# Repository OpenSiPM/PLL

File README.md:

## Overview

Resonant scanning is essential for high-speed and *in vivo* laser scanning microscopy. However, resonant scanners are susceptible to jitter due to a mismatch between the mirror's mechanical oscillation and the data acquisition system's pixel sampling clock. If the digitizer samples at a fixed rate, the pixels on one line land in slightly different positions than on the next and the raw data appears shifted from line to line.

Our solution is to generate the digitizer sample clock **from the resonant scanner's own sync signal** using a PLL. Every line is then sampled at the same scanner phase, so the pixel grid follows the scanner rather than drifting against it. The method runs in real time, is entirely electrical and requires no software changes, so it can be easily incorporated into most existing microscopy systems. 

This approach is described and validated in:

> Ching-Roa VD, Huang CZ, Giacomelli MG. **Suppression of Subpixel Jitter in Resonant Scanning Systems With Phase-locked Sampling.** *IEEE Transactions on Medical Imaging* 43(6):2159–2168, 2024. [doi:10.1109/TMI.2024.3358191](https://doi.org/10.1109/TMI.2024.3358191) · [PubMed 38265914](https://pubmed.ncbi.nlm.nih.gov/38265914/)

The repository is organized into separate folders: PLL_AD9544 contains the KiCAD design files for the board, Configuration Files contains the AD9544 register configurations and a script to convert them into EEPROM images, and EEPROM_writer together with PLL_EEPROM_upload.m are used to program the configuration onto the board.

## AD9544 PLL Board 
This PCB receives the resonant scanner sync signal, locks to it using an Analog Devices AD9544 clock generator, and outputs a phase-locked sample clock for the digitizer and a line trigger. The AD9544 is referenced to a 52 MHz crystal, and its configuration is stored in a 24AA16 I2C EEPROM, which the AD9544 loads automatically at power-up. A SAMD21 microcontroller receives commands over USB and is used to program the EEPROM. Power is supplied over USB and regulated down to 3.3 V and 1.8 V, and a PLL LOCK LED indicates when the PLL has locked to the reference.

- **J1 (USB):** power and EEPROM programming
- **J3 (output):** phase-locked pixel sample clock to the digitizer
- **J4 (output):** line trigger at the scanner frequency
- **J5 (input):** resonant scanner sync signal (8 kHz or 12 kHz)

See: [PLL_AD9544](PLL_AD9544). [Bill of materials](https://htmlpreview.github.io/?https://github.com/tikagergaia/PLL/blob/main/PLL_AD9544/ibom.html)

## Configuration files
1. The AD9544 is configured through its registers, which are designed using the [Analysis|Control|Evaluation(ACE) Software Version 1.10.2671.1118](https://swdownloads.analog.com/ACE/ACEInstall_1.10.2671.1118.exe). *Do not update it to newer versions as they are not tested with the AD9544 plug-in module.* In ACE, set up the reference input, DPLL, output frequencies, and loop bandwidth. The ACE session can then be exported as a `.cso` file for the register settings.

   The PLL LOCK LED is driven by the AD9544's M0 multifunction pin (M-pin), which is set up in ACE as a lock status output:

2. Use the `ad9545_create_eeprom_bin.py` script to generate bin files for EEPROM. Set `fn` in the script to your `.cso` file and run it from inside the `Configuration Files` folder (it needs `bitarray.py` and `defaults.txt`, which are in the same folder). It writes a `.bin` file with the same name as the `.cso`.

Sample files for 8 kHz and 12 kHz scanners are available in the `Configuration Files` folder (both `.cso` and ready-to-upload `.bin` files are included).

The approach does not depend on the AD9544. Other clock chips (for example, the AD9545) can do the same job. They need their own configuration files and EEPROM image, but the principle stays the same.

## Programming EEPROM
The EEPROM_writer folder contains the Arduino sketch for the SAMD21 microcontroller, which requires the [I2C_eeprom](https://github.com/RobTillaart/I2C_EEPROM) library. On startup, the sketch reports the EEPROM size and the scanner frequency currently stored in it.

To program a configuration onto the board:

1. Upload `EEPROM_writer/EEPROM_writer.ino` to the SAMD21 using the Arduino IDE.
2. Open `PLL_EEPROM_upload.m` in MATLAB, set the path to your `.bin` file (e.g. `Configuration Files/12kHz_LED.bin`) and the board's COM port (`'COMX'`), and run the script. It sends the `program` command followed by the 1280-byte image, reads the EEPROM contents back and compares checksums. "Checksum of file matches uploaded data." means the upload succeeded.
3. Power-cycle the board. The AD9544 loads its configuration from the EEPROM, and the PLL LOCK LED lights once a valid reference is connected.

## Ordering boards

Go to https://jlcpcb.com, https://www.seeedstudio.com/fusion_pcb.html or the service of your choice, upload the Gerber files, and pay.

Gerber files can be generated from KiCAD using 'File -> Plot' or using the JLCPCB Fabrication Toolkit plugin (settings are included in `PLL_AD9544/fabrication-toolkit-options.json`).

## Board assembly

The easiest way to assemble this board is using solder paste and a reflow oven or hotplate. The AD9544 comes in a 48-lead LFCSP package with an exposed ground pad, and most of the passives are 0402, so reflow is strongly recommended over hand soldering. If you're going to make several boards, paying for assembly of the passive and common components might be worthwhile.

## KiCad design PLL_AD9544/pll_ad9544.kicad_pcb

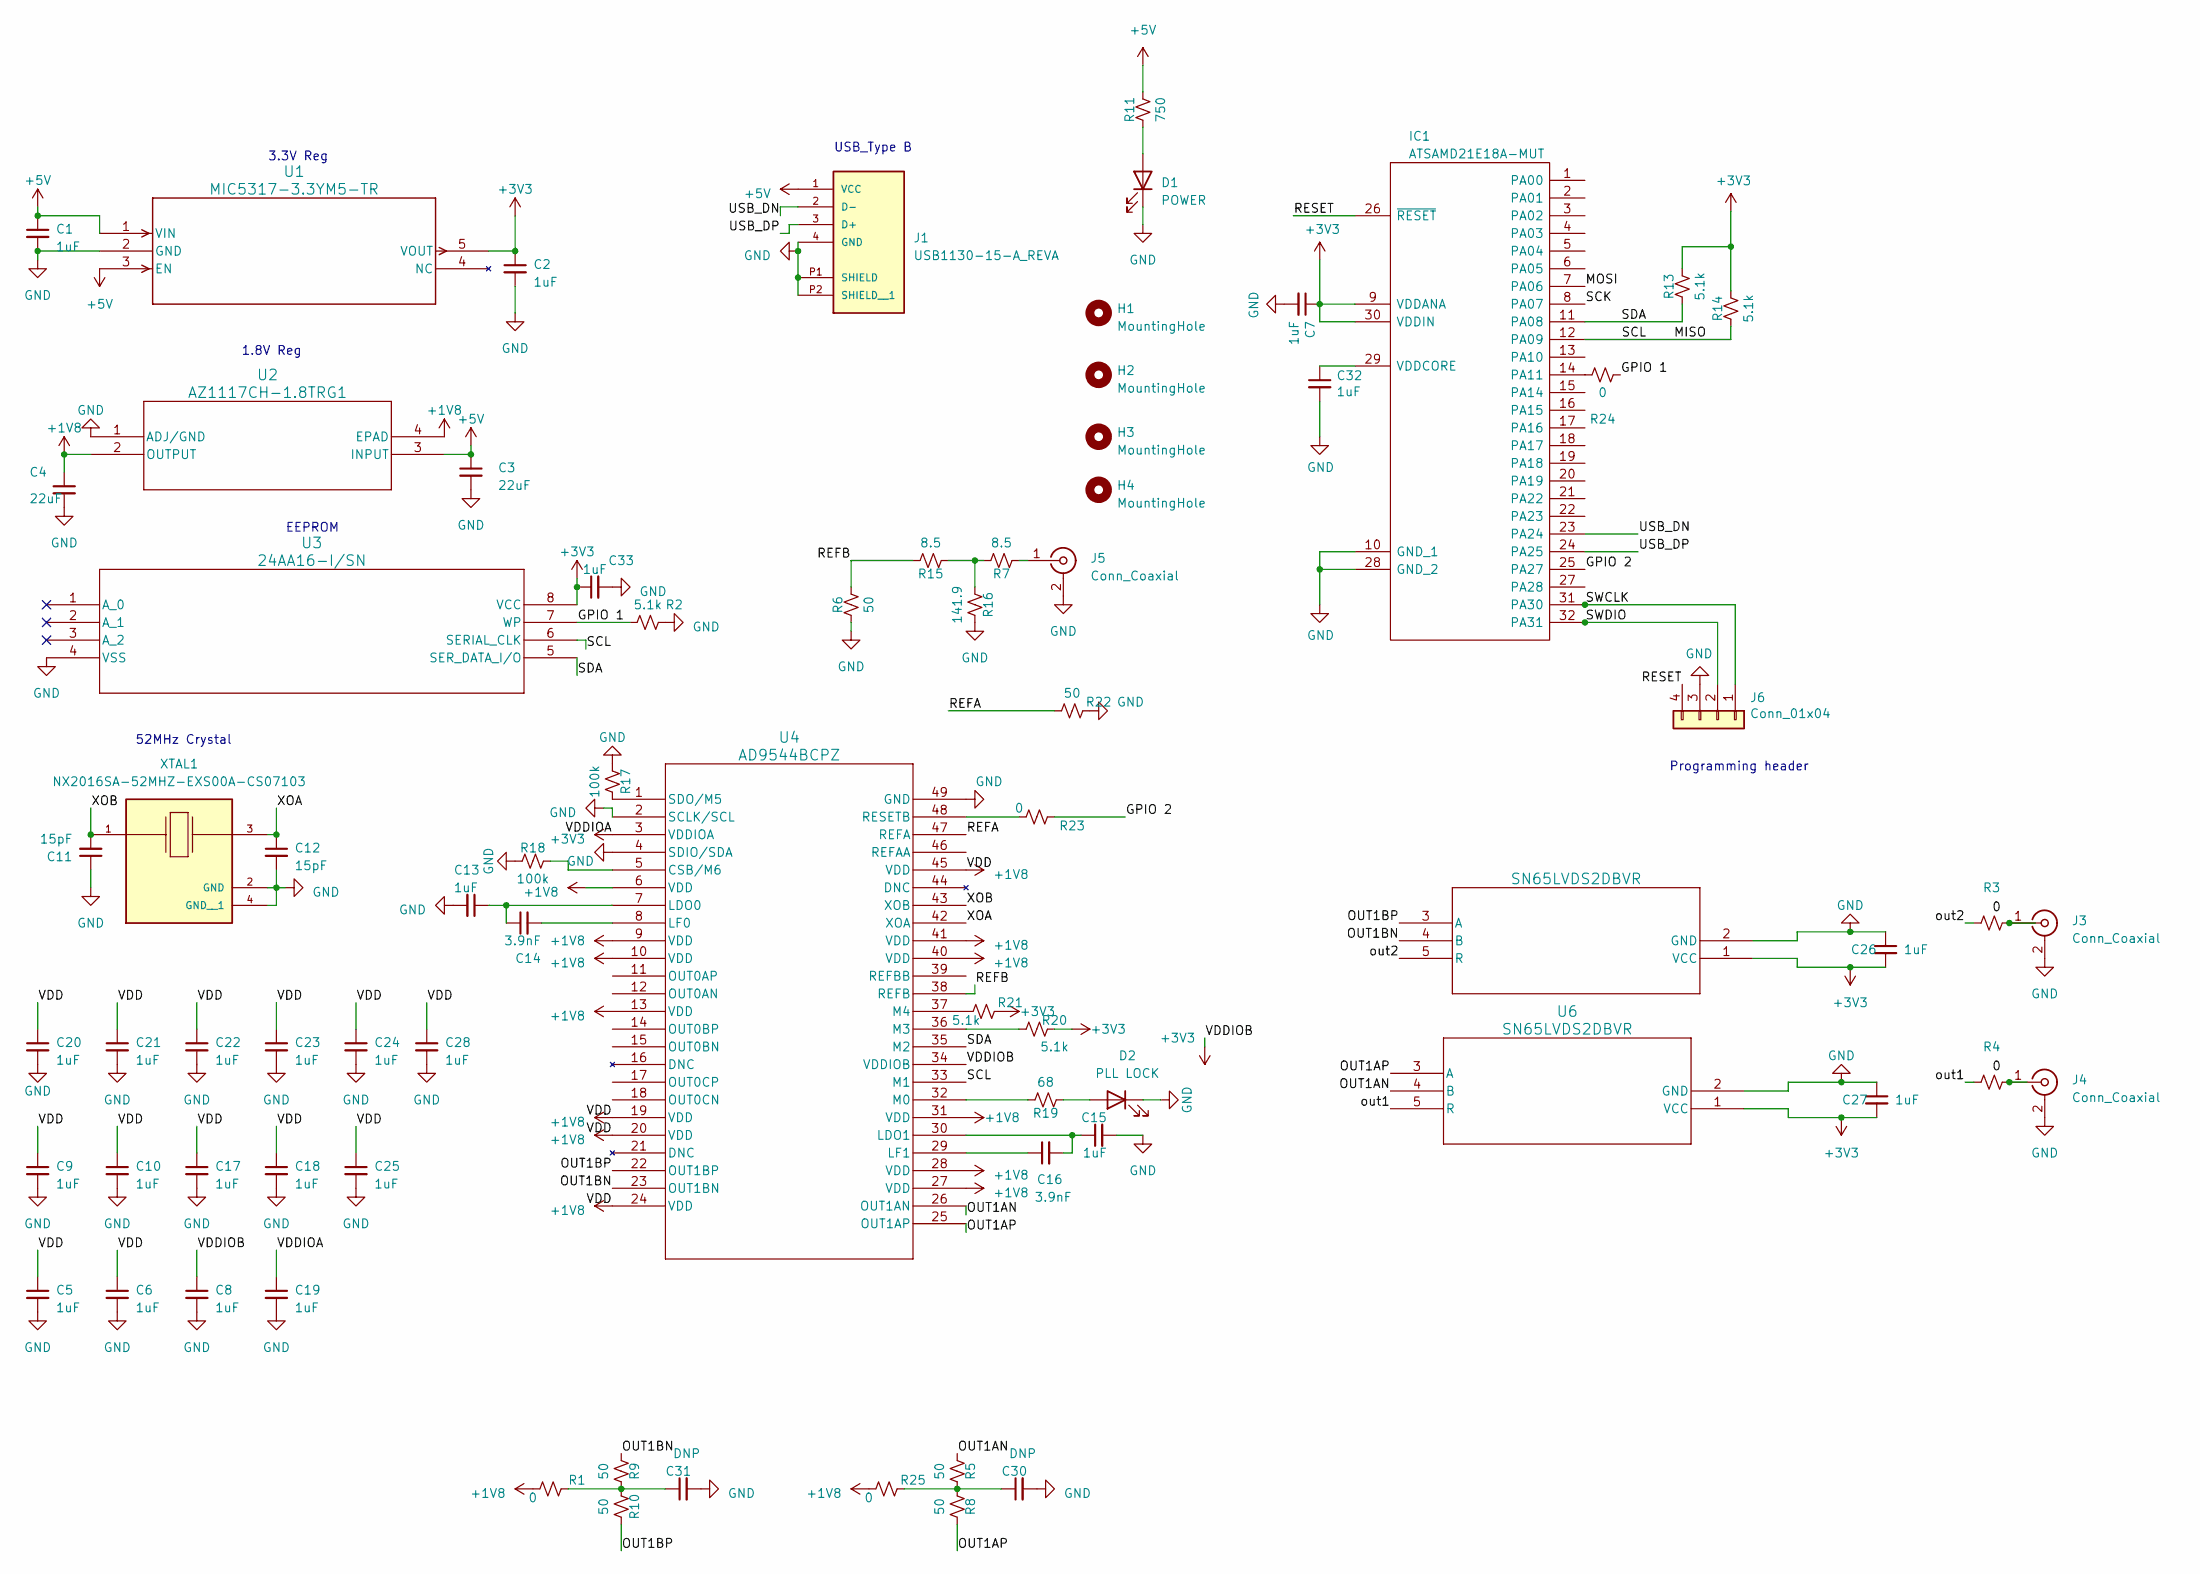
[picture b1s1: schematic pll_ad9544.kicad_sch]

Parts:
C1, C2, C5, C6, C7, C8, C9, C10, C13, C15, C17, C18, C19, C20, C21, C22, C23, C24, C25, C26, C27, C28, C32, C33: 1uF; C_0402_1005Metric
C3, C4: 22uF; C_0603_1608Metric
C11, C12: 15pF; C_0402_1005Metric
C14, C16: 3.9nF; C_0402_1005Metric
C30, C31: DNP; C_0402_1005Metric
D1: POWER; LED_0603_1608Metric
D2: PLL LOCK; LED_0603_1608Metric
H1, H2, H3, H4: MountingHole; MountingHole_2.5mm
IC1: ATSAMD21E18A-MUT; TQFP32_MC_MCH; Manufacturer_Part_Number ATSAMD21E18A-AFT
J1: USB1130-15-A_REVA; OST_USB-B1HSB6; PARTREV A
J3, J4, J5: Conn_Coaxial; SMA_Amphenol_901-144_Vertical
J6: Conn_01x04; PinHeader_1x04_P2.54mm_Vertical_SMD_Pin1Left
R1, R23, R24, R25: 0; R_0402_1005Metric
R2, R13, R14, R20, R21: 5.1k; R_0402_1005Metric
R3, R4: R_Small_US; R_0402_1005Metric
R5, R6, R8, R9, R10, R22: 50; R_0402_1005Metric
R7, R15: 8.5; R_0402_1005Metric
R11: 750; R_0402_1005Metric
R16: 141.9; R_0402_1005Metric
R17, R18: 100k; R_0402_1005Metric
R19: 68; R_0402_1005Metric
U1: MIC5317-3.3YM5-TR; SOT-23-5_M5_MCH
U2: AZ1117CH-1.8TRG1; SOT-223_DIO
U3: 24AA16-I/SN; SOIC8-N_MC_MCH
U4: AD9544BCPZ; CP-48-13_ADI
U5, U6: SN65LVDS2DBVR; DBV5
XTAL1: NX2016SA-52MHZ-EXS00A-CS07103; OSCCC200X160X50N; PARTREV N/A

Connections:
+1V8: C4.1, C5.1, C6.1, C9.1, C10.1, C17.1, C18.1, C20.1, C21.1, C22.1, C23.1, C24.1, C25.1, C28.1, R1.2, R25.2, U2.2 (OUTPUT), U2.4 (EPAD), U4.6 (VDD), U4.9 (VDD), U4.10 (VDD), U4.13 (VDD), U4.19 (VDD), U4.20 (VDD), U4.24 (VDD), U4.27 (VDD), U4.28 (VDD), U4.31 (VDD), U4.40 (VDD), U4.41 (VDD), U4.45 (VDD)
+3V3: C2.1, C7.1, C8.1, C19.1, C26.2, C27.2, C33.1, IC1.9 (VDDANA), IC1.30 (VDDIN), R13.1, R14.1, R20.1, R21.1, U1.5 (VOUT), U3.8 (VCC), U4.3 (VDDIOA), U4.34 (VDDIOB), U5.1 (VCC), U6.1 (VCC)
+5V: C1.1, C3.1, J1.1 (VCC), R11.1, U1.1 (VIN), U1.3 (EN), U2.3 (INPUT)
/GPIO 1: R2.1, R24.1, U3.7 (WP)
/GPIO 2: IC1.25 (PA27), R23.1
/MISO: IC1.12 (PA09), R14.2, U3.6 (SERIAL_CLK), U4.33 (M1)
/MOSI: IC1.7 (PA06)
/OUT1AN: R5.2, U4.26 (OUT1AN), U6.4 (B)
/OUT1AP: R8.1, U4.25 (OUT1AP), U6.3 (A)
/OUT1BN: R9.2, U4.23 (OUT1BN), U5.4 (B)
/OUT1BP: R10.1, U4.22 (OUT1BP), U5.3 (A)
/REFA: R22.2, U4.47 (REFA)
/REFB: R6.1, R15.1, U4.38 (REFB)
/RESET: IC1.26 (~RESET), J6.4
/SCK: IC1.8 (PA07)
/SDA: IC1.11 (PA08), R13.2, U3.5 (SER_DATA_I/O), U4.35 (M2)
/SWCLK: IC1.31 (PA30), J6.1
/SWDIO: IC1.32 (PA31), J6.2
/USB_DN: IC1.23 (PA24), J1.2 (D-)
/USB_DP: IC1.24 (PA25), J1.3 (D+)
/XOA: C12.1, U4.42 (XOA), XTAL1.3
/XOB: C11.2, U4.43 (XOB), XTAL1.1
/out1: R4.2, U6.5 (R)
/out2: R3.2, U5.5 (R)
GND: C1.2, C2.2, C3.2, C4.2, C5.2, C6.2, C7.2, C8.2, C9.2, C10.2, C11.1, C12.2, C13.2, C15.2, C17.2, C18.2, C19.2, C20.2, C21.2, C22.2, C23.2, C24.2, C25.2, C26.1, C27.1, C28.2, C30.2, C31.2, C32.2, C33.2, D1.1 (K), D2.1 (K), IC1.10 (GND_1), IC1.28 (GND_2), IC1.33 (EP), J1.4 (GND), J1.P1 (SHIELD), J1.P2 (SHIELD__1), J3.2 (Ext), J4.2 (Ext), J5.2 (Ext), J6.3, R2.2, R6.2, R16.1, R17.2, R18.2, R22.1, U1.2 (GND), U2.1 (ADJ/GND), U3.4 (VSS), U4.2 (SCLK/SCL), U4.4 (SDIO/SDA), U4.49 (GND), U5.2 (GND), U6.2 (GND), XTAL1.2 (GND), XTAL1.4 (GND__1); also elsewhere on the board
unnamed: C30.1, R5.1, R8.2, R25.1
unnamed: C31.1, R1.1, R9.1, R10.2
unnamed: D1.2 (A), R11.2
unnamed: D2.2 (A), R19.2
unnamed: IC1.14 (PA11), R24.2
unnamed: C32.1, IC1.29 (VDDCORE)
unnamed: J3.1 (In), R3.1
unnamed: J4.1 (In), R4.1
unnamed: J5.1 (In), R7.2
unnamed: R7.1, R15.2, R16.2
unnamed: R18.1, U4.5 (CSB/M6)
unnamed: C13.1, C14.1, U4.7 (LDO0)
unnamed: C15.1, C16.2, U4.30 (LDO1)
unnamed: C14.2, U4.8 (LF0)
unnamed: C16.1, U4.29 (LF1)
unnamed: R19.1, U4.32 (M0)
unnamed: R20.2, U4.36 (M3)
unnamed: R21.2, U4.37 (M4)
unnamed: R23.2, U4.48 (RESETB)
unnamed: R17.1, U4.1 (SDO/M5)

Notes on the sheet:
EEPROM
USB_Type B
Programming header
1.8V Reg
3.3V Reg
52MHz Crystal

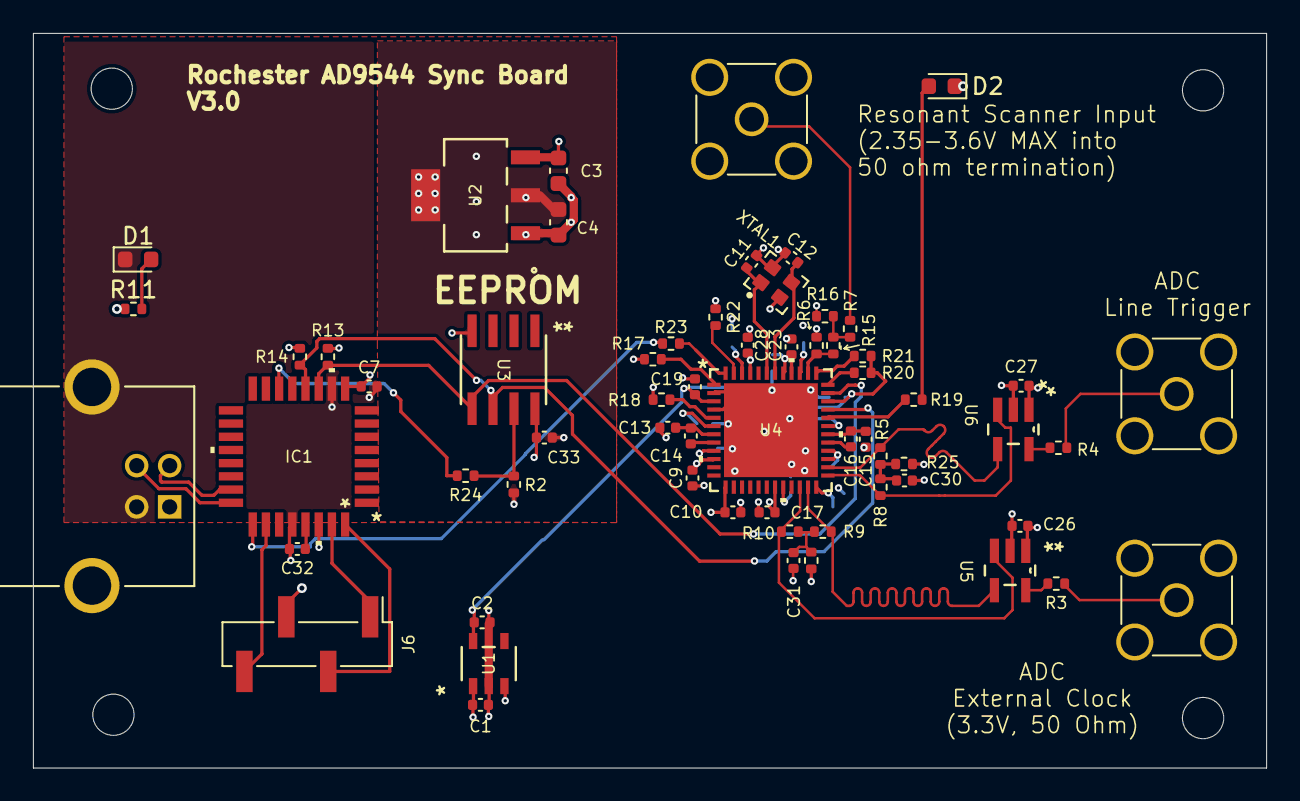
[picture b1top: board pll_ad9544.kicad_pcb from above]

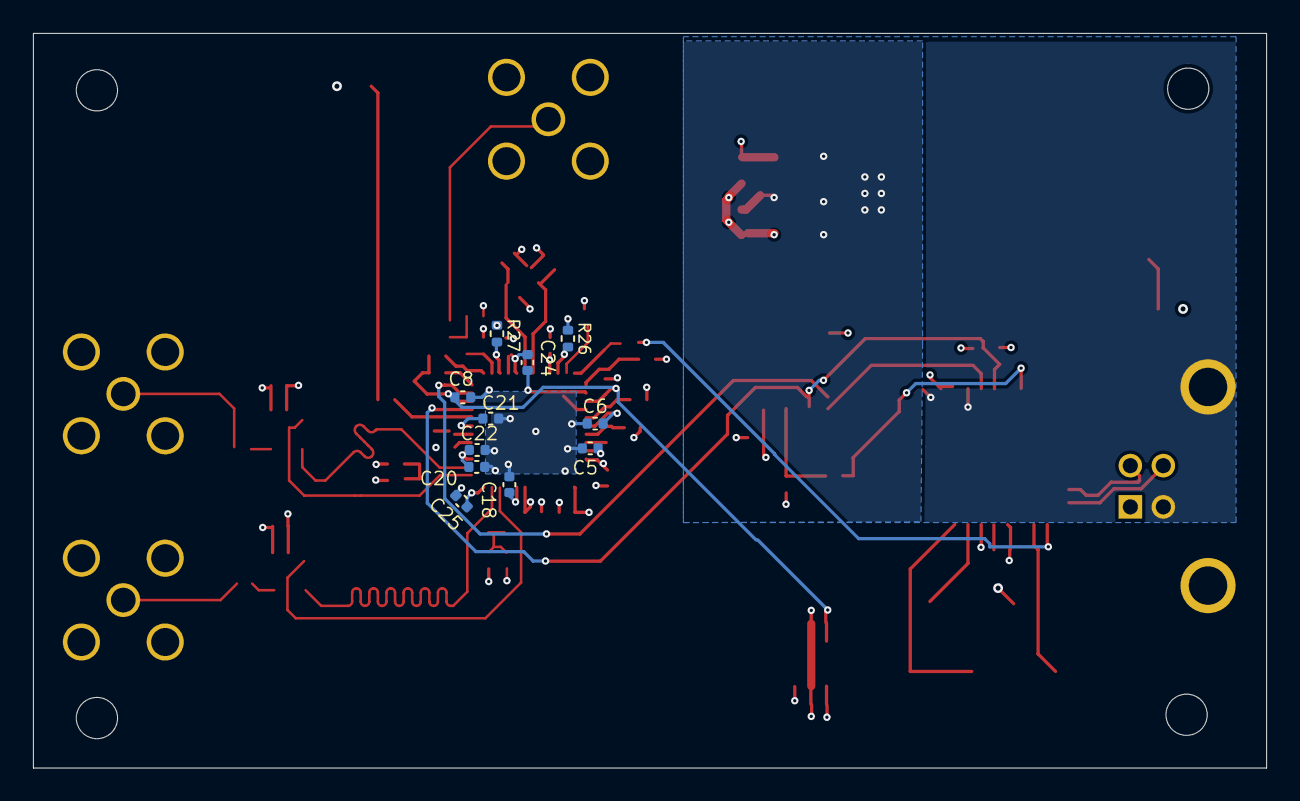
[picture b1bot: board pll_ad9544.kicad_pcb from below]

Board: 4 copper layers, 74.8 x 44.5 mm, 77 parts (11 on the bottom side), 43 nets.

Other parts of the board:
R26, R27: 50; R_0402_1005Metric

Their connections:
GND: R26.1, R27.1; also elsewhere on the board
